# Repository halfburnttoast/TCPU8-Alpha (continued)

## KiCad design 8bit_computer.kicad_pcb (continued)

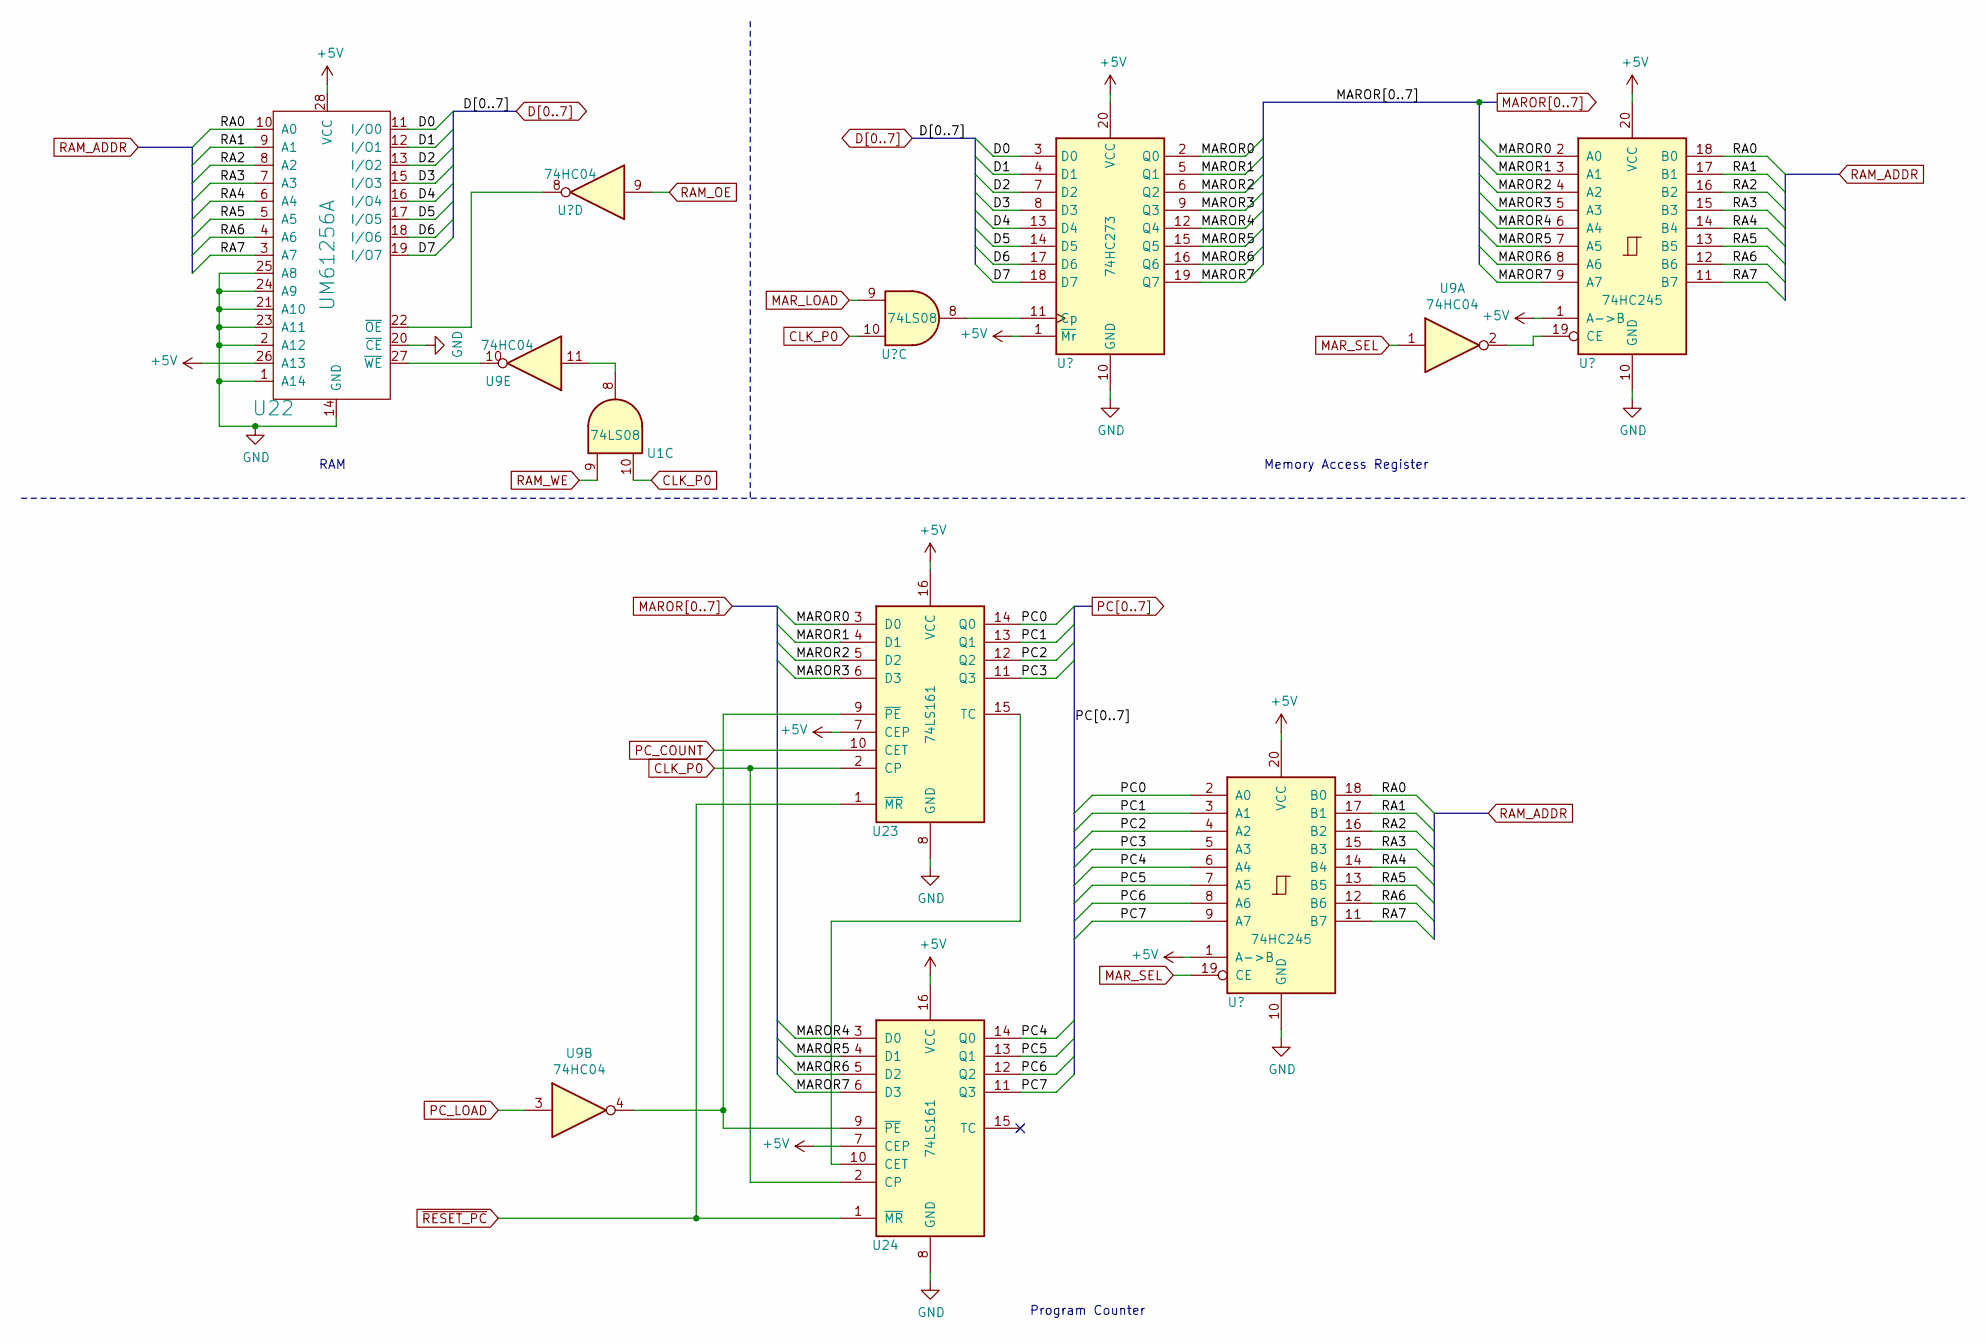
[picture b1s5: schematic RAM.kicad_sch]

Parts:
U1, U10: 74LS08; DIP-14_W7.62mm
U9: 74HC04; DIP-14_W7.62mm
U22: UM61256A; DIP-28_W7.62mm
U23, U24: 74LS161; DIP-16_W7.62mm
U25: 74HC273; DIP-20_W7.62mm
U26, U27: 74HC245; DIP-20_W7.62mm

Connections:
+5V: U22.26 (A13), U22.28 (VCC), U23.7 (CEP), U23.16 (VCC), U24.7 (CEP), U24.16 (VCC), U25.1 (~Mr), U25.20 (VCC), U26.1 (A->B), U26.20 (VCC), U27.1 (A->B), U27.20 (VCC); also elsewhere on the board
/Sheet632E549A/RA0: U22.10 (A0), U26.18 (B0), U27.18 (B0)
/Sheet632E549A/RA1: U22.9 (A1), U26.17 (B1), U27.17 (B1)
/Sheet632E549A/RA2: U22.8 (A2), U26.16 (B2), U27.16 (B2)
/Sheet632E549A/RA3: U22.7 (A3), U26.15 (B3), U27.15 (B3)
/Sheet632E549A/RA4: U22.6 (A4), U26.14 (B4), U27.14 (B4)
/Sheet632E549A/RA5: U22.5 (A5), U26.13 (B5), U27.13 (B5)
/Sheet632E549A/RA6: U22.4 (A6), U26.12 (B6), U27.12 (B6)
/Sheet632E549A/RA7: U22.3 (A7), U26.11 (B7), U27.11 (B7)
CLK_P0: U1.10, U10.10, U23.2 (CP), U24.2 (CP); also elsewhere on the board
D0: U22.11 (I/O0), U25.3 (D0); also elsewhere on the board
D1: U22.12 (I/O1), U25.4 (D1); also elsewhere on the board
D2: U22.13 (I/O2), U25.7 (D2); also elsewhere on the board
D3: U22.15 (I/O3), U25.8 (D3); also elsewhere on the board
D4: U22.16 (I/O4), U25.13 (D4); also elsewhere on the board
D5: U22.17 (I/O5), U25.14 (D5); also elsewhere on the board
D6: U22.18 (I/O6), U25.17 (D6); also elsewhere on the board
D7: U22.19 (I/O7), U25.18 (D7); also elsewhere on the board
GND: U22.1 (A14), U22.2 (A12), U22.14 (GND), U22.20 (~CE), U22.21 (A10), U22.23 (A11), U22.24 (A9), U22.25 (A8), U23.8 (GND), U24.8 (GND), U25.10 (GND), U26.10 (GND), U27.10 (GND); also elsewhere on the board
MAROR0: U23.3 (D0), U25.2 (Q0), U27.2 (A0); also elsewhere on the board
MAROR1: U23.4 (D1), U25.5 (Q1), U27.3 (A1); also elsewhere on the board
MAROR2: U23.5 (D2), U25.6 (Q2), U27.4 (A2); also elsewhere on the board
MAROR3: U23.6 (D3), U25.9 (Q3), U27.5 (A3); also elsewhere on the board
MAROR4: U24.3 (D0), U25.12 (Q4), U27.6 (A4); also elsewhere on the board
MAROR5: U24.4 (D1), U25.15 (Q5), U27.7 (A5); also elsewhere on the board
MAROR6: U24.5 (D2), U25.16 (Q6), U27.8 (A6); also elsewhere on the board
MAROR7: U24.6 (D3), U25.19 (Q7), U27.9 (A7); also elsewhere on the board
MAR_LOAD: U10.9; also elsewhere on the board
MAR_SEL: U9.1, U26.19 (CE); also elsewhere on the board
unnamed: U1.8, U9.11
unnamed: U10.8, U25.11 (Cp)
unnamed: U9.8, U22.22 (~OE)
unnamed: U9.10, U22.27 (~WE)
unnamed: U9.4, U23.9 (~PE), U24.9 (~PE)
unnamed: U23.15 (TC), U24.10 (CET)
unnamed: U9.2, U27.19 (CE)
PC0: U23.14 (Q0), U26.2 (A0); also elsewhere on the board
PC1: U23.13 (Q1), U26.3 (A1); also elsewhere on the board
PC2: U23.12 (Q2), U26.4 (A2); also elsewhere on the board
PC3: U23.11 (Q3), U26.5 (A3); also elsewhere on the board
PC4: U24.14 (Q0), U26.6 (A4); also elsewhere on the board
PC5: U24.13 (Q1), U26.7 (A5); also elsewhere on the board
PC6: U24.12 (Q2), U26.8 (A6); also elsewhere on the board
PC7: U24.11 (Q3), U26.9 (A7); also elsewhere on the board
PC_COUNT: U23.10 (CET); also elsewhere on the board
PC_LOAD: U9.3; also elsewhere on the board
RAM_OE: U9.9; also elsewhere on the board
RAM_WE: U1.9; also elsewhere on the board
~RESET_PC: U23.1 (~MR), U24.1 (~MR); also elsewhere on the board

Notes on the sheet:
Program Counter
RAM
Memory Access Register

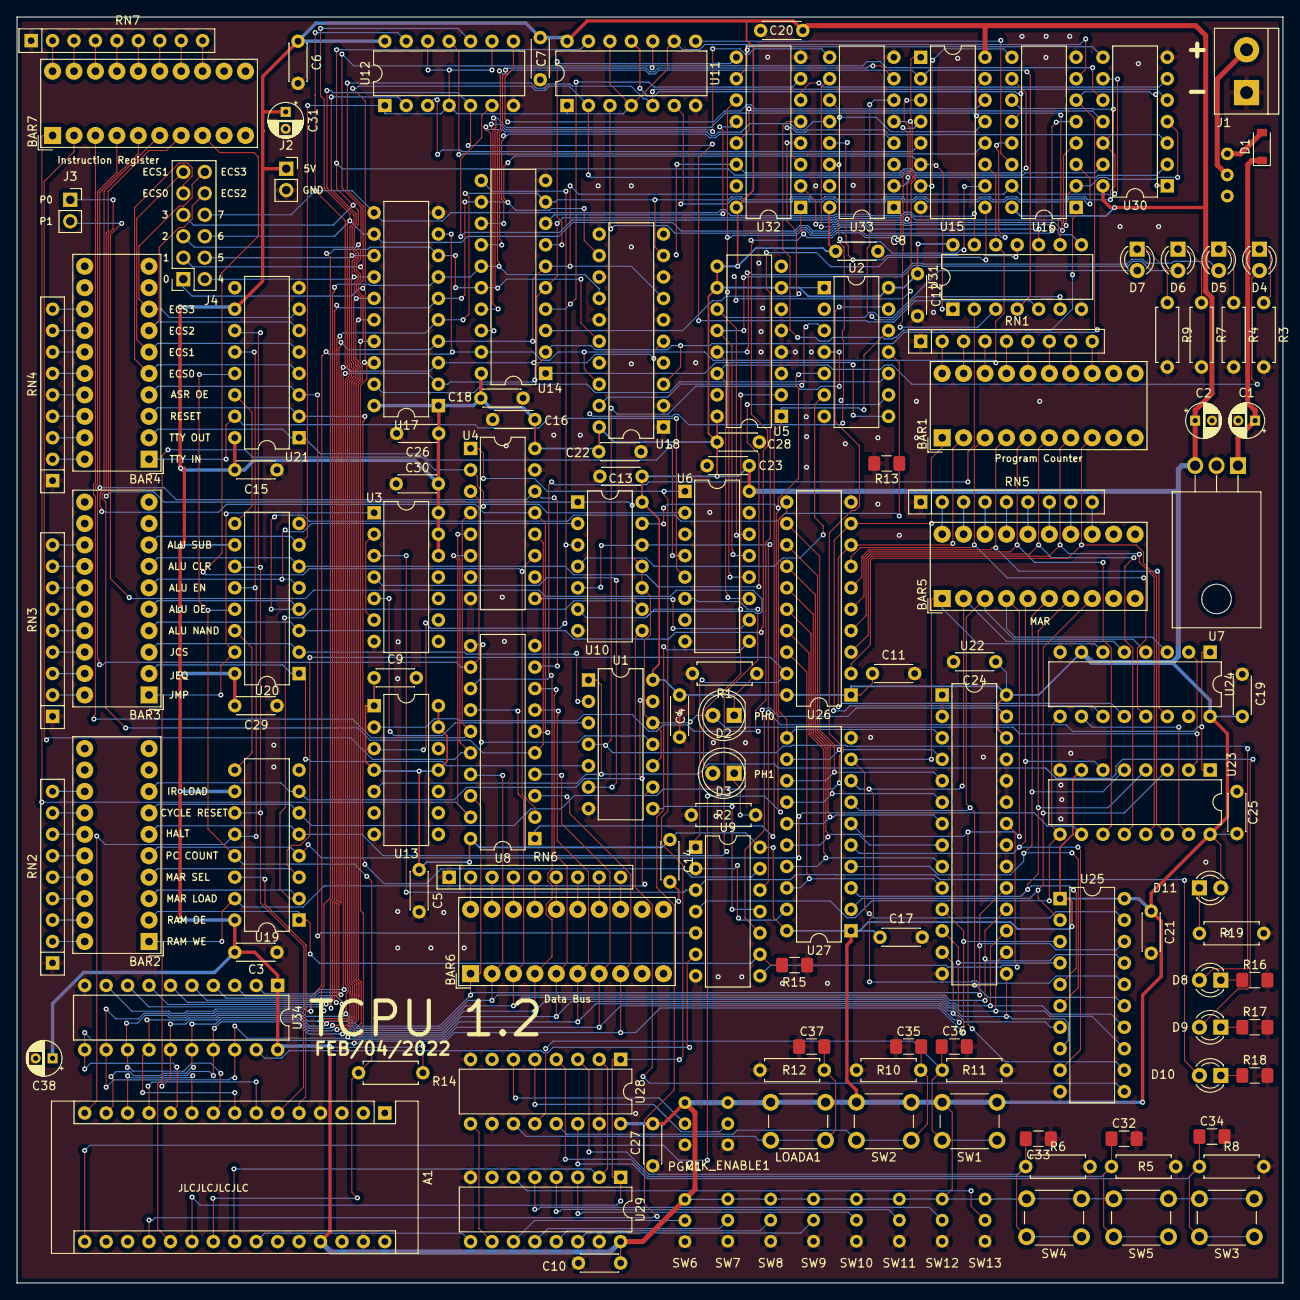
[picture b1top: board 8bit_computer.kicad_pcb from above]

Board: 2 copper layers, 150.0 x 150.0 mm, 138 parts (0 on the bottom side), 235 nets.

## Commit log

2024-08-25 Latest update
2024-08-25 Added PDF schematic
